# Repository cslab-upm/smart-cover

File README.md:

## Smart Cover

Este dispositivo es una tapa inteligente para un telescopio que abre y cierra según la hora del día. El diseño se puede parametrizar para que cualquiera pueda adaptarlo al tamaño de su telescopio.

### Diseño mecánico

Diseños y Planos necesarios para construir la tapa del telescopio. Dentro podrá encontrarse una excel para calcular los parámetros necesarios de fabricación en base al diámetro de la tapa.

### PCB

Se incluye el plano electrónico y el archivo para construir la PCB.

### Firmware

Firmware necesario para controlar la tapa del telescopio robótico. Desarrollado para microcontrolador ESP32.

Para más detalles sobre los pasos a seguir, ver: [Instructables](https://www.instructables.com/Smart-Cover-of-a-Night-time-Telescope-for-Day-time/).

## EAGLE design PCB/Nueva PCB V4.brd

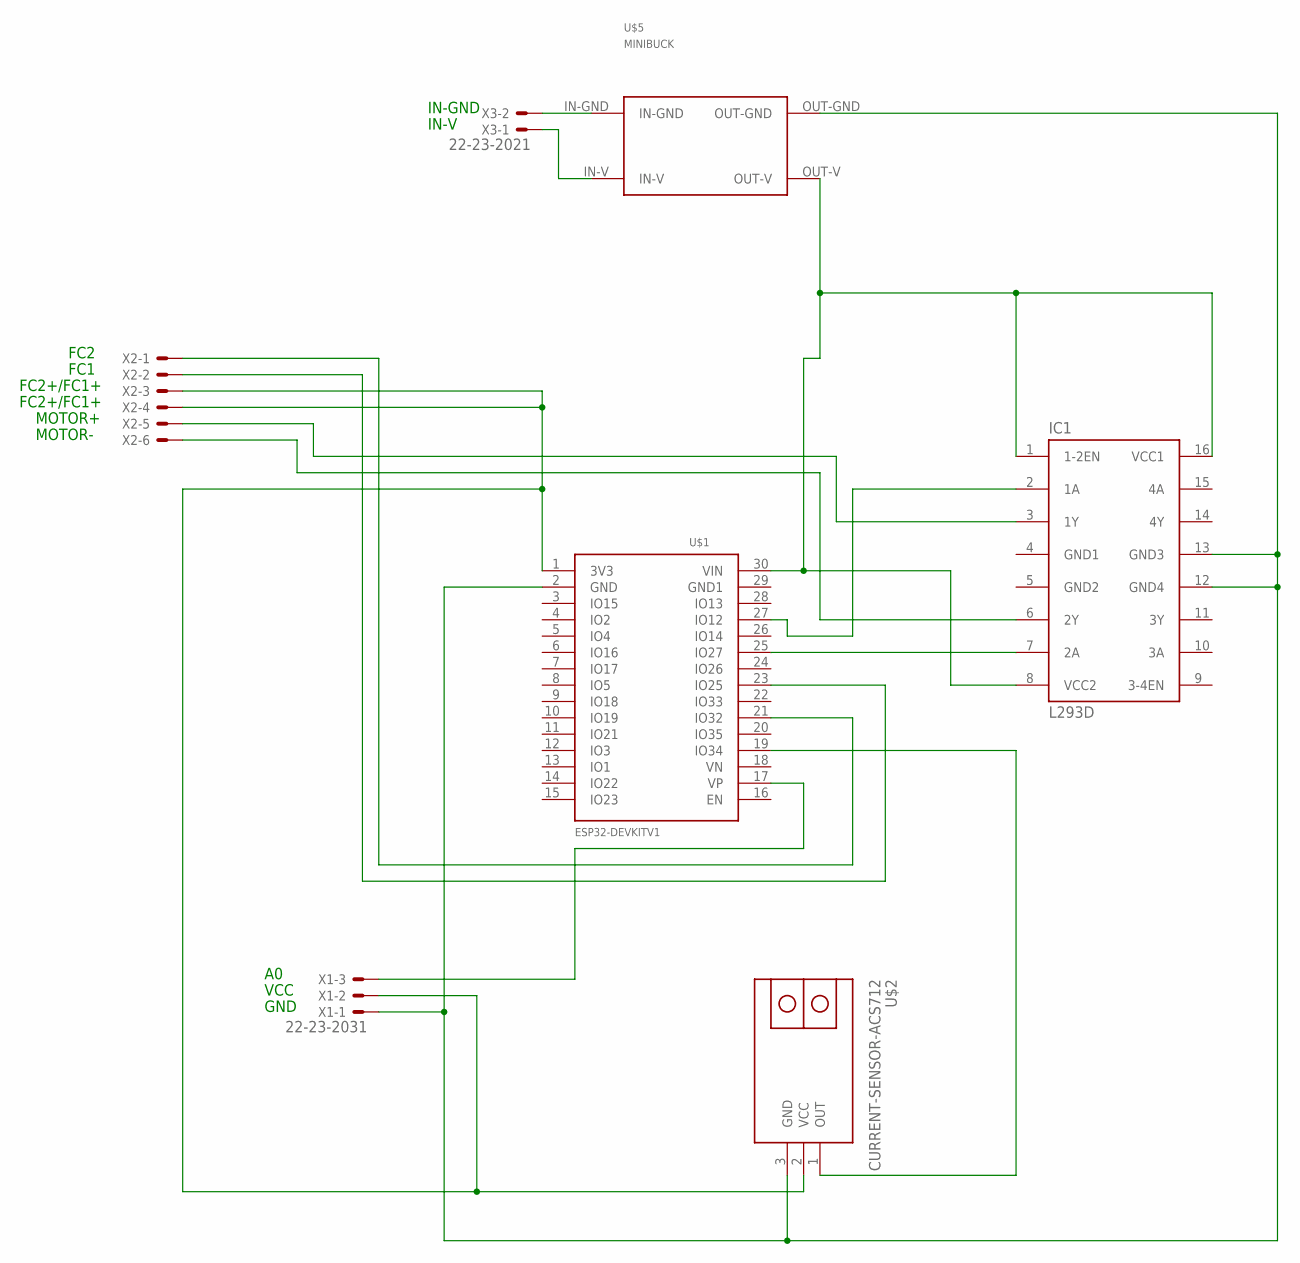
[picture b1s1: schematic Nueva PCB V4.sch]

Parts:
IC1: L293D; DIL16
U$1: ESP32DEVKITV1; ESP32-DEVKITV1
U$2: CURRENT-SENSOR-ACS712
U$5: MINIBUCK; BUCK4PINES
X1: 22-23-2031
X2: 22-23-2061
X3: 22-23-2021

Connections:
GND: IC1.12 (GND4), IC1.13 (GND3), U$1.2 (GND), U$2.3 (GND), U$5.OUT-GND, X1.1
GND1: IC1.4 (GND1)
GND2: IC1.5 (GND2)
unnamed: U$5.IN-GND, X3.2
unnamed: U$5.IN-V, X3.1
unnamed: IC1.1 (1-2EN), IC1.8 (VCC2), IC1.16 (VCC1), U$1.30 (VIN), U$5.OUT-V
unnamed: IC1.3 (1Y), X2.5
unnamed: IC1.6 (2Y), X2.6
unnamed: IC1.2 (1A), U$1.27 (IO12)
unnamed: IC1.7 (2A), U$1.25 (IO27)
unnamed: U$1.1 (3V3), U$2.2 (VCC), X1.2, X2.3, X2.4
unnamed: U$1.23 (IO25), X2.2
unnamed: U$1.19 (IO34), U$2.1 (OUT)
unnamed: U$1.17 (VP), X1.3
unnamed: U$1.21 (IO32), X2.1

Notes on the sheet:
FC2
FC1
FC2+/FC1+
MOTOR+
MOTOR-
VCC
GND
IN-GND
IN-V

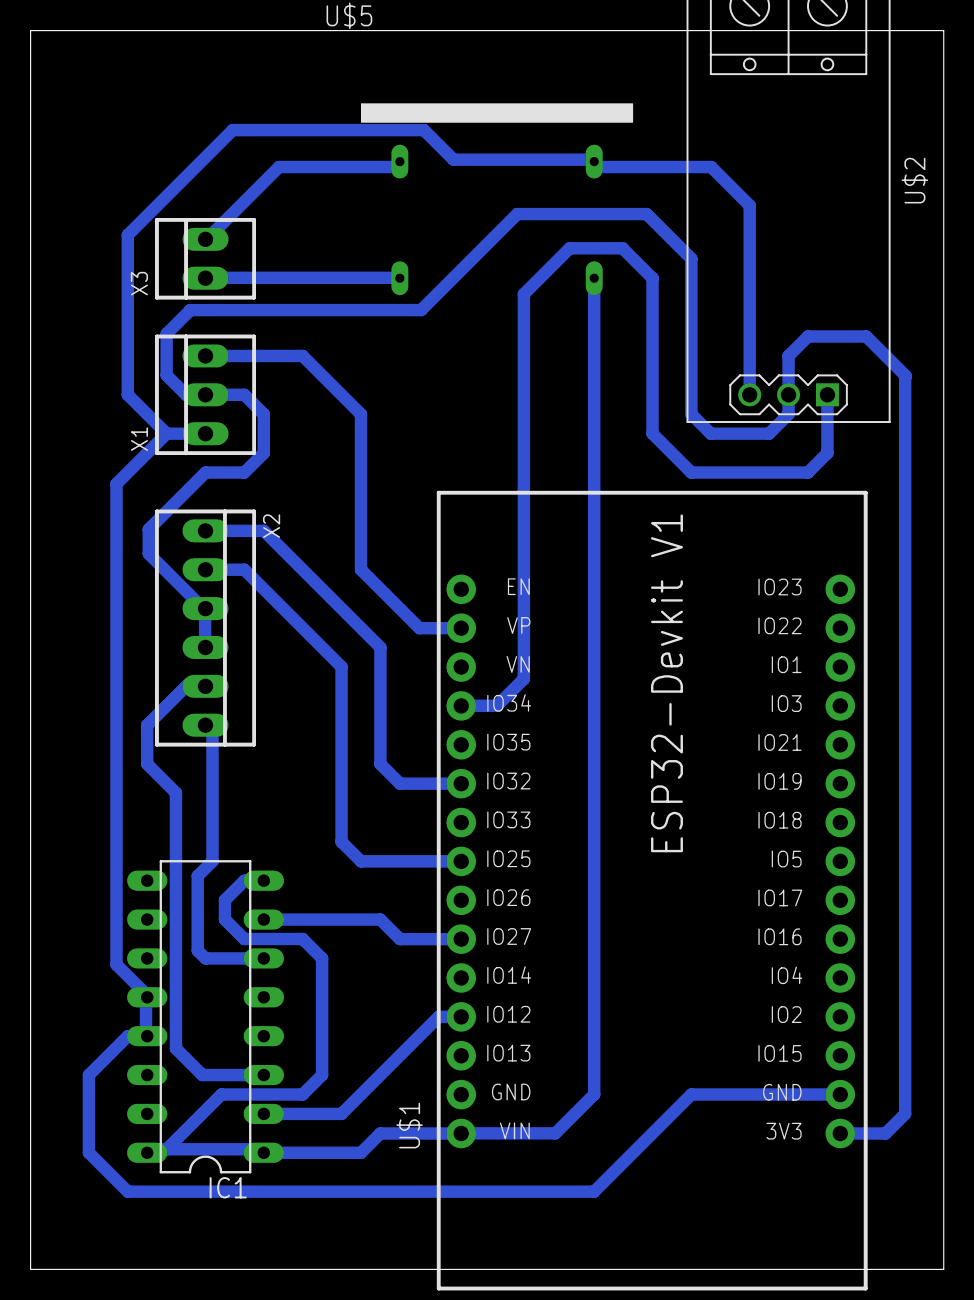
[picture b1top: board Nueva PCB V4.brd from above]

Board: 2 copper layers, 59.7 x 81.0 mm, 7 parts (0 on the bottom side), 13 nets.

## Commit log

2020-04-08 Set theme jekyll-theme-architect
2021-01-04 First release
    All parts of the project uploaded: PCB, Mechanical design and Firmware

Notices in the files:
parts and their libraries:
diy-modules: Released under the Creative Commons Attribution 4.0 International License: http://creativecommons.org/licenses/by/4.0
